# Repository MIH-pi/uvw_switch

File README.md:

# uvw_switch
A three-phase motor 3PDT relay switch

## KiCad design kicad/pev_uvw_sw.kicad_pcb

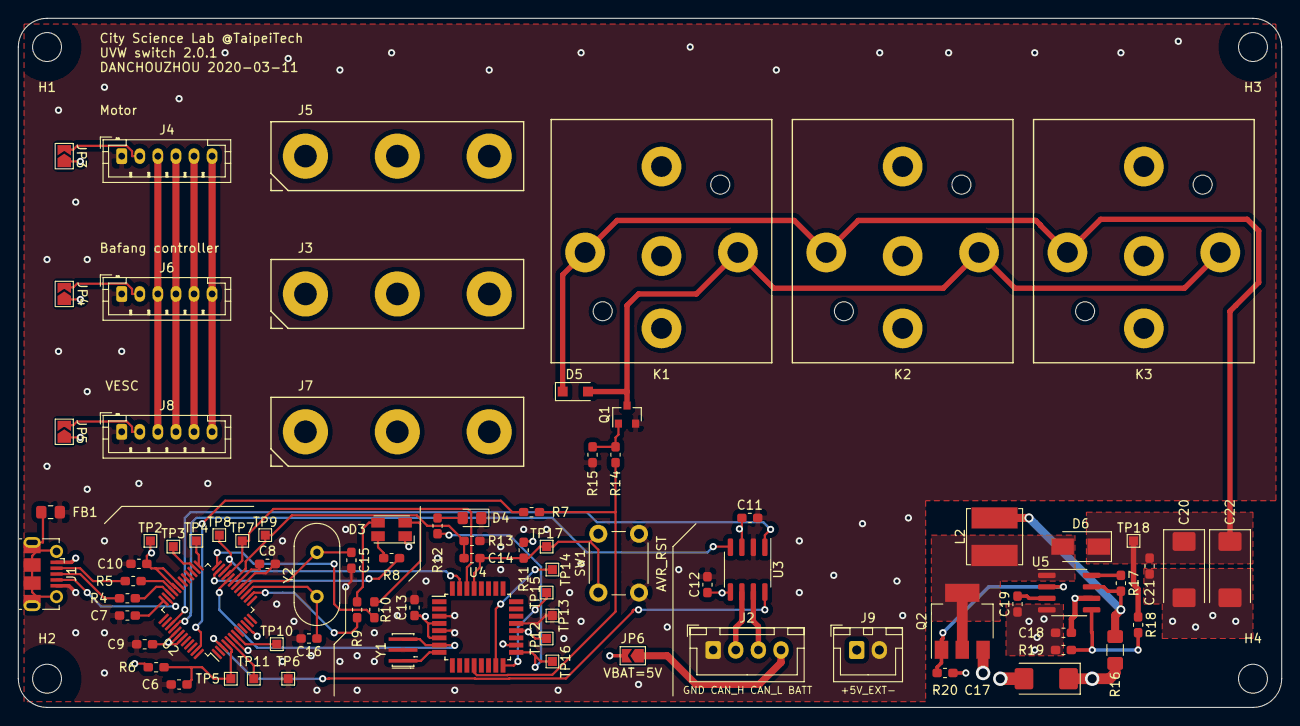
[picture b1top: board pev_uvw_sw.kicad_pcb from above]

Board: 4 copper layers, 139.7 x 76.2 mm, 86 parts (0 on the bottom side), 66 nets.

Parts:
C6, C9, C10, C11, C12, C13, C14: 100nF; C_0603_1608Metric_Pad1.05x0.95mm_HandSolder
C7, C8, C18, C21: 1uF; C_0603_1608Metric_Pad1.05x0.95mm_HandSolder
C15, C16: 18pF; C_0603_1608Metric_Pad1.05x0.95mm_HandSolder
C17: 100uF; CP_EIA-6032-28_Kemet-C
C19: 330pF; C_0603_1608Metric_Pad1.05x0.95mm_HandSolder
C20, C22: 47uF; CP_EIA-7343-43_Kemet-X
D3: CLV1L-FKB; LED_Avago_PLCC4_3.2x2.8mm_CW
D4: LED; LED_0805_2012Metric_Pad1.15x1.40mm_HandSolder
D5: MBR130LSFT1G; D_SOD-123F
D6: SS14; D_SMA
FB1: Ferrite_Bead; L_0805_2012Metric_Pad1.15x1.40mm_HandSolder
H1, H2, H3, H4: MountingHole; MountingHole_3.2mm_M3_DIN965
J1: 1050170001; USB_Micro-B_Molex-105017-0001
J2: CAN bus; JST_XH_B4B-XH-A_1x04_P2.50mm_Vertical
J3: CTRL; motor_uvw_only_conn
J4: CTRL; JST_PH_B6B-PH-K_1x06_P2.00mm_Vertical
J5: MOTOR; motor_uvw_only_conn
J6: MOTOR; JST_PH_B6B-PH-K_1x06_P2.00mm_Vertical
J7: VESC; motor_uvw_only_conn
J8: VESC; JST_PH_B6B-PH-K_1x06_P2.00mm_Vertical
J9: 5V_EXT; JST_XH_B02B-XH-A_1x02_P2.50mm_Vertical
JP3, JP4, JP5: SolderJumper-2_P1.3mm_Open_TrianglePad1.0x1.5mm
JP6: SolderJumper; SolderJumper-2_P1.3mm_Open_TrianglePad1.0x1.5mm
K1, K2, K3: 1432870-1; TE_Relay_VCF4-1000_PCB_Socket
L2: SRN6045TA-220M; L_Bourns_SRN6045TA
Q1: MMBT2222A; SOT-23
Q2: NZT560A; SOT-223-3_TabPin2
R4, R5: 33R; R_0603_1608Metric_Pad1.05x0.95mm_HandSolder
R6, R11: 10K; R_0603_1608Metric_Pad1.05x0.95mm_HandSolder
R7, R12, R13, R14, R15: 1K; R_0603_1608Metric_Pad1.05x0.95mm_HandSolder
R8: 300R; R_0603_1608Metric_Pad1.05x0.95mm_HandSolder
R9, R10: 240R; R_0603_1608Metric_Pad1.05x0.95mm_HandSolder
R16: 0R12; R_1206_3216Metric_Pad1.42x1.75mm_HandSolder
R17: 180R; R_0603_1608Metric_Pad1.05x0.95mm_HandSolder
R18: 20K; R_0603_1608Metric_Pad1.05x0.95mm_HandSolder
R19: 1K1; R_0603_1608Metric_Pad1.05x0.95mm_HandSolder
R20: 3K6; R_0603_1608Metric_Pad1.05x0.95mm_HandSolder
SW1: AVRRST; SW_PUSH_6mm_H4.3mm
TP2, TP12: 5V; TestPoint_Pad_1.0x1.0mm
TP3: DAT; TestPoint_Pad_1.0x1.0mm
TP4: CLK; TestPoint_Pad_1.0x1.0mm
TP5, TP17: RST; TestPoint_Pad_1.0x1.0mm
TP6, TP13: GND; TestPoint_Pad_1.0x1.0mm
TP7: M4_TXD; TestPoint_Pad_1.0x1.0mm
TP8: M4_RXD; TestPoint_Pad_1.0x1.0mm
TP9: M4_DTR; TestPoint_Pad_1.0x1.0mm
TP10: DEBUG_TXD; TestPoint_Pad_1.0x1.0mm
TP11: DEBUG_RXD; TestPoint_Pad_1.0x1.0mm
TP14: MOSI; TestPoint_Pad_1.0x1.0mm
TP15: MISO; TestPoint_Pad_1.0x1.0mm
TP16: SCK; TestPoint_Pad_1.0x1.0mm
TP18: 24V; TestPoint_Pad_1.0x1.0mm
U2: M453_LQFP48; LQFP-48_7x7mm_P0.5mm
U3: TCAN1042V-Q1; SOIC-8_3.9x4.9mm_P1.27mm
U4: ATmega328P-AU; TQFP-32_7x7mm_P0.8mm
U5: MC33063AD; SOIC-8_3.9x4.9mm_P1.27mm
Y1: CSTNE16M0V530000R0; Resonator_SMD_muRata_CSTxExxV-3Pin_3.0x1.1mm_HandSoldering
Y2: X12M; Crystal_HC49-U_Vertical

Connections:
+5V: C9.1, C10.1, C11.1, C12.1, C13.1, C17.1, C18.1, D3.1, J1.1, J9.1, JP3.1, JP4.1, JP5.1, JP6.2, R6.1, R11.2, R16.2, TP2.1, TP12.1, U2.10, U2.31, U2.32, U2.41, U2.42, U2.43, U3.3, U3.5, U4.4, U4.6, U4.18, U4.20, U5.6
+24V: C20.1, C21.1, C22.1, D5.1, D6.1, K1.5, K2.5, K3.5, R18.1, TP18.1
+BATT: J2.4, JP6.1
/Arduino compatible/RST: C14.2, R11.1, SW1.1, TP17.1, U4.29
/Interface gateway/CAN_RX: U2.40, U3.4
/Interface gateway/CAN_STB: U2.3, U3.8
/Interface gateway/CAN_TX: U2.39, U3.1
/Interface gateway/DEBUG_RXD: TP11.1, U2.5
/Interface gateway/DEBUG_TXD: TP10.1, U2.7
/Interface gateway/XTI: C15.1, U2.16, Y2.1
/Interface gateway/XTO: C16.1, U2.15, Y2.2
/Relays/RYOC: D5.2, K1.2, K2.2, K3.2, Q1.3
/Relays/RYUA: J7.1, K1.3
/Relays/RYUB: J3.1, K1.4
/Relays/RYUC: J5.1, K1.1
/Relays/RYVA: J7.2, K2.3
/Relays/RYVB: J3.2, K2.4
/Relays/RYVC: J5.2, K2.1
/Relays/RYWA: J7.3, K3.3
/Relays/RYWB: J3.3, K3.4
/Relays/RYWC: J5.3, K3.1
GND: C6.2, C7.2, C8.2, C9.2, C10.2, C11.2, C12.2, C13.2, C15.2, C16.2, C17.2, C18.2, C19.1, C20.2, C21.2, C22.2, D4.1, FB1.2, J1.5, J2.1, J4.1, J6.1, J8.1, J9.2, Q1.2, Q2.3, R13.1, R15.2, R19.2, R20.2, SW1.2, TP6.1, TP13.1, U2.6, U2.17, U3.2, U4.3, U4.5, U4.21, U5.4, Y1.2
M4_CKO: U2.20, U4.7, Y1.3
M4_DTR: C14.1, R13.2, TP9.1, U2.19
M4_RXD: TP8.1, U2.22, U4.31
M4_TXD: TP7.1, U2.21, U4.30
unnamed: C6.1, R6.2, TP5.1, U2.4
unnamed: C7.1, U2.36
unnamed: C8.1, U2.18
unnamed: C19.2, U5.3
unnamed: D3.2, R8.1
unnamed: D3.3, R9.1
unnamed: D3.4, R10.1
unnamed: D4.2, R12.1
unnamed: D6.2, L2.2, Q2.2, U5.1
unnamed: FB1.1, J1.6
unnamed: J1.2, R5.2
unnamed: J1.3, R4.2
unnamed: J1.4, U2.35
unnamed: J2.2, U3.6
unnamed: J2.3, U3.7
unnamed: J4.2, JP3.2
unnamed: J4.3, J6.3, J8.3
unnamed: J4.4, J6.4, J8.4
unnamed: J4.5, J6.5, J8.5
unnamed: J4.6, J6.6, J8.6
unnamed: J6.2, JP4.2
unnamed: J8.2, JP5.2
unnamed: L2.1, R16.1, R17.2, U5.7
unnamed: Q1.1, R14.1, R15.1
unnamed: Q2.1, R20.1, U5.2
unnamed: R4.1, U2.34
unnamed: R5.1, U2.33
unnamed: R7.2, U2.47
unnamed: R8.2, U2.23
unnamed: R9.2, U2.14
unnamed: R10.2, U2.24
unnamed: R12.2, TP16.1, U4.17
unnamed: R17.1, U5.8
unnamed: R18.2, R19.1, U5.5
unnamed: TP3.1, U2.26
unnamed: TP4.1, U2.25
unnamed: TP14.1, U4.15
unnamed: TP15.1, U4.16
unnamed: U4.8, Y1.1
RELAY: R7.1, R14.2, U4.12

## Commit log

2022-05-31 Add .gitignore
2022-06-06 Add kicad files
2022-06-06 Update schematic
2022-06-13 Add submodule
2022-07-27 Add USB to serial firmware
2022-07-27 Update Makefile
2022-07-27 Add 16KB ld script
2022-07-27 Update ld script
2022-07-27 Add project template
2022-07-27 Update main function
